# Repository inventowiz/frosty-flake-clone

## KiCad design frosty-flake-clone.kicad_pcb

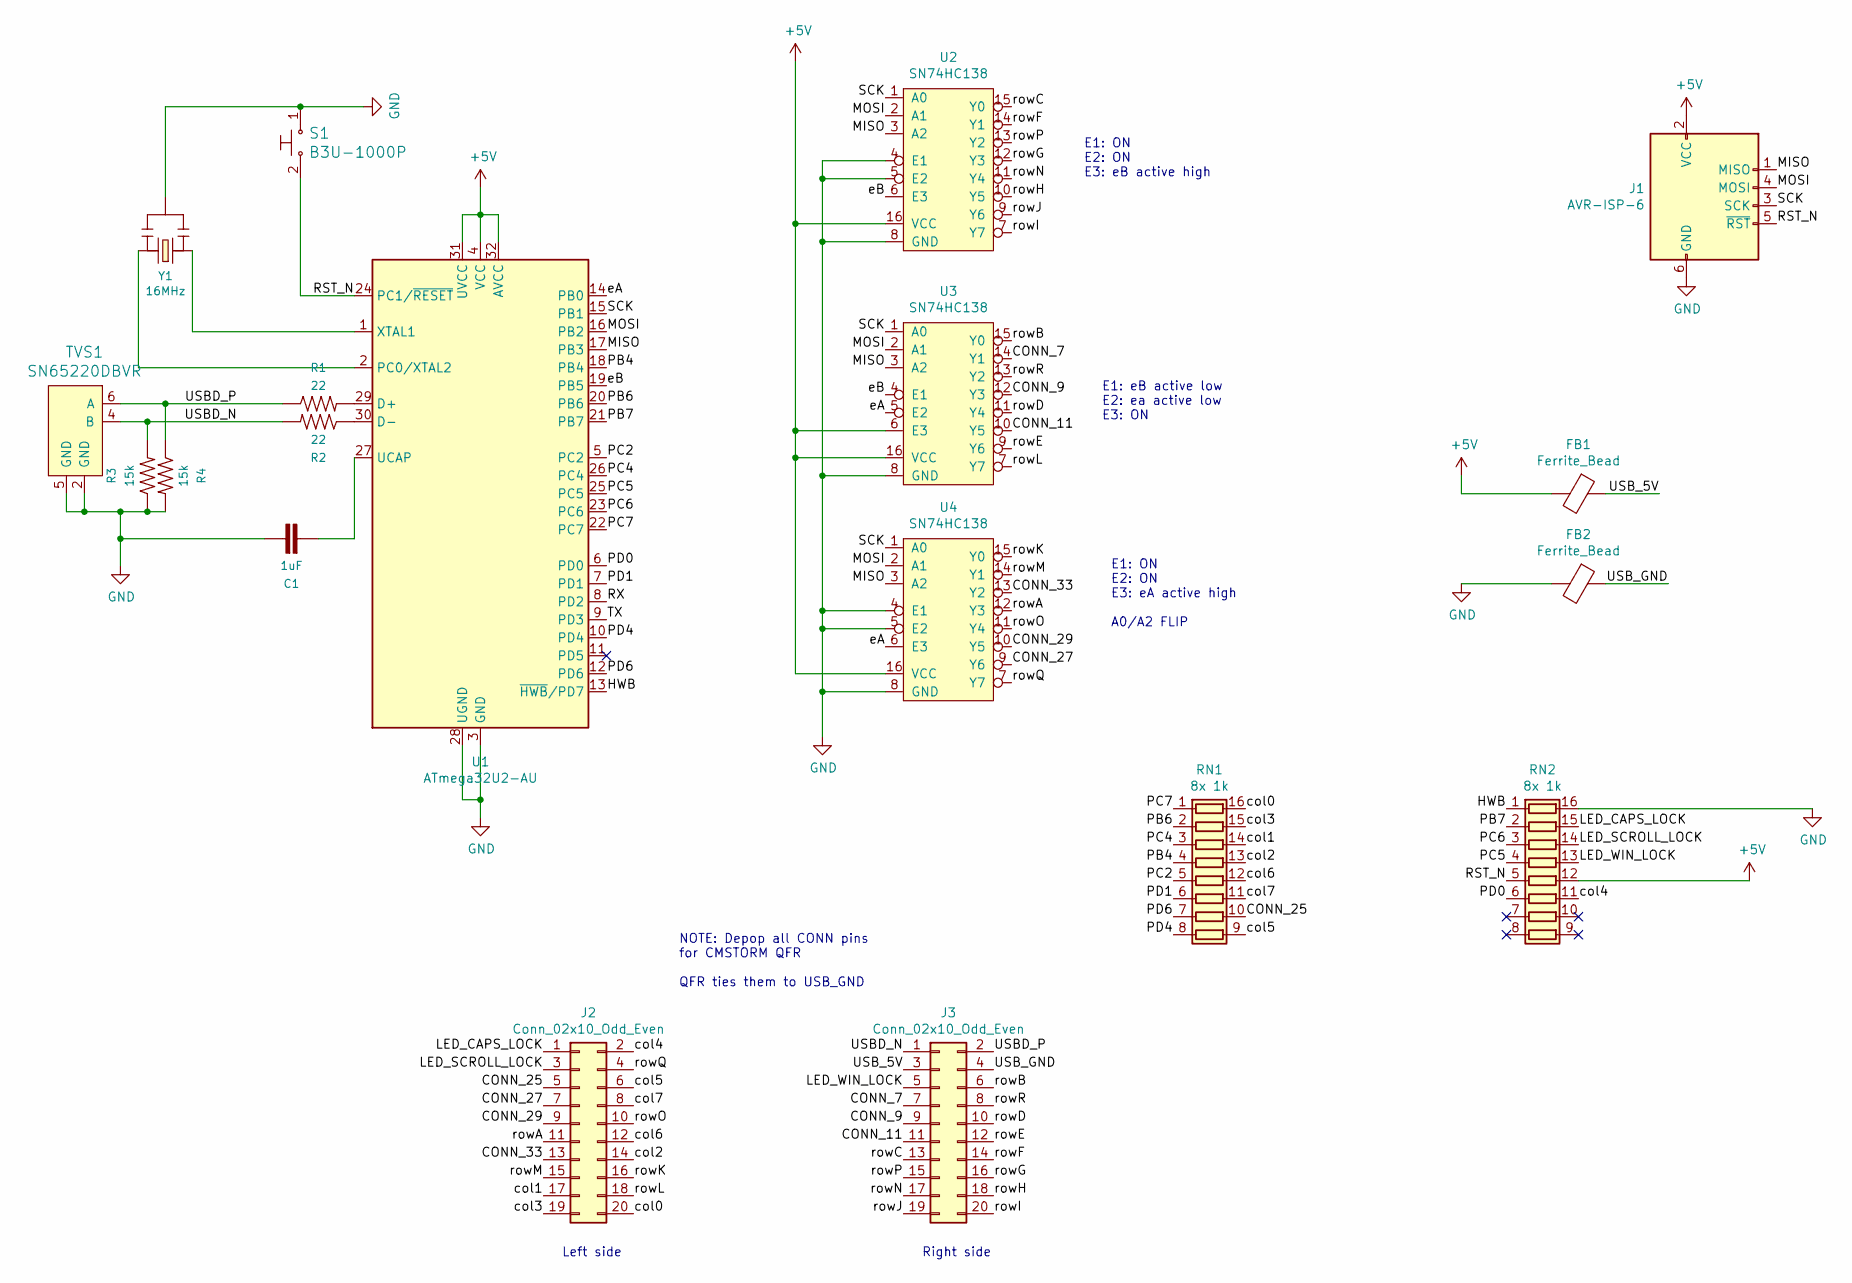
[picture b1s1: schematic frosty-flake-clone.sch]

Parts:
C1: 1uF; 0805
FB1, FB2: Ferrite_Bead; 0603
J1: AVR-ISP-6; 2X3
J2, J3: Conn_02x10_Odd_Even; PinHeader_2x10_P2.00mm_Vertical
R1, R2: 22; 0603
R3, R4: 15k; 0603
RN1, RN2: 8x 1k; R_Array_Convex_8x0602
S1: B3U-1000P; Switch_Tactile_SMD_B3U-1000P; MPN B3U-1000P; Digi-Key_PN SW1020CT-ND
TVS1: SN65220DBVR; SOT-23-6; MPN SN65220DBVR; Digi-Key_PN 296-9694-1-ND
U1: ATmega32U2-AU; TQFP-32_7x7mm_P0.8mm
U2, U3, U4: SN74HC138; TSSOP16
Y1: 16MHz; RESONATOR-SMD-3.2X1.3

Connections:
+5V: FB1.2, J1.2 (VCC), RN2.12 (R5.2), U1.4 (VCC), U1.31 (UVCC), U1.32 (AVCC), U2.16 (VCC), U3.6 (E3), U3.16 (VCC), U4.16 (VCC)
/CONN_7: J3.7, U3.14 (Y1)
/CONN_9: J3.9, U3.12 (Y3)
/CONN_11: J3.11, U3.10 (Y5)
/CONN_25: J2.5, RN1.10 (R7.2)
/CONN_27: J2.7, U4.9 (Y6)
/CONN_29: J2.9, U4.10 (Y5)
/CONN_33: J2.13, U4.13 (Y2)
/HWB: RN2.1 (R1.1), U1.13 (~HWB~/PD7)
/LED_CAPS_LOCK: J2.1, RN2.15 (R2.2)
/LED_SCROLL_LOCK: J2.3, RN2.14 (R3.2)
/LED_WIN_LOCK: J3.5, RN2.13 (R4.2)
/MISO: J1.1 (MISO), U1.17 (PB3), U2.3 (A2), U3.3 (A2), U4.3 (A2)
/MOSI: J1.4 (MOSI), U1.16 (PB2), U2.2 (A1), U3.2 (A1), U4.2 (A1)
/PB4: RN1.4 (R4.1), U1.18 (PB4)
/PB6: RN1.2 (R2.1), U1.20 (PB6)
/PB7: RN2.2 (R2.1), U1.21 (PB7)
/PC2: RN1.5 (R5.1), U1.5 (PC2)
/PC4: RN1.3 (R3.1), U1.26 (PC4)
/PC5: RN2.4 (R4.1), U1.25 (PC5)
/PC6: RN2.3 (R3.1), U1.23 (PC6)
/PC7: RN1.1 (R1.1), U1.22 (PC7)
/PD0: RN2.6 (R6.1), U1.6 (PD0)
/PD1: RN1.6 (R6.1), U1.7 (PD1)
/PD4: RN1.8 (R8.1), U1.10 (PD4)
/PD6: RN1.7 (R7.1), U1.12 (PD6)
/RST_N: J1.5 (~RST), RN2.5 (R5.1), S1.2, U1.24 (PC1/~RESET)
/RX: U1.8 (PD2)
/SCK: J1.3 (SCK), U1.15 (PB1), U2.1 (A0), U3.1 (A0), U4.1 (A0)
/TX: U1.9 (PD3)
/USBD_N: J3.1, R2.2, R3.2, TVS1.4 (B)
/USBD_P: J3.2, R1.1, R4.1, TVS1.6 (A)
/USB_5V: FB1.1, J3.3
/USB_GND: FB2.1, J3.4
/col0: J2.20, RN1.16 (R1.2)
/col1: J2.17, RN1.14 (R3.2)
/col2: J2.14, RN1.13 (R4.2)
/col3: J2.19, RN1.15 (R2.2)
/col4: J2.2, RN2.11 (R6.2)
/col5: J2.6, RN1.9 (R8.2)
/col6: J2.12, RN1.12 (R5.2)
/col7: J2.8, RN1.11 (R6.2)
/eA: U1.14 (PB0), U3.5 (E2), U4.6 (E3)
/eB: U1.19 (PB5), U2.6 (E3), U3.4 (E1)
/rowA: J2.11, U4.12 (Y3)
/rowB: J3.6, U3.15 (Y0)
/rowC: J3.13, U2.15 (Y0)
/rowD: J3.10, U3.11 (Y4)
/rowE: J3.12, U3.9 (Y6)
/rowF: J3.14, U2.14 (Y1)
/rowG: J3.16, U2.12 (Y3)
/rowH: J3.18, U2.10 (Y5)
/rowI: J3.20, U2.7 (Y7)
/rowJ: J3.19, U2.9 (Y6)
/rowK: J2.16, U4.15 (Y0)
/rowL: J2.18, U3.7 (Y7)
/rowM: J2.15, U4.14 (Y1)
/rowN: J3.17, U2.11 (Y4)
/rowO: J2.10, U4.11 (Y4)
/rowP: J3.15, U2.13 (Y2)
/rowQ: J2.4, U4.7 (Y7)
/rowR: J3.8, U3.13 (Y2)
GND: C1.1, FB2.2, J1.6 (GND), R3.1, R4.2, RN2.16 (R1.2), S1.1, TVS1.2 (GND), TVS1.5 (GND), U1.3 (GND), U1.28 (UGND), U2.4 (E1), U2.5 (E2), U2.8 (GND), U3.8 (GND), U4.4 (E1), U4.5 (E2), U4.8 (GND), Y1.2
unnamed: C1.2, U1.27 (UCAP)
unnamed: R1.2, U1.29 (D+)
unnamed: R2.1, U1.30 (D-)
unnamed: U1.1 (XTAL1), Y1.1
unnamed: U1.2 (PC0/XTAL2), Y1.3

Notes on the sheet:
Right side
Left side
E1: eB active low E2: ea active low E3: ON
E1: ON E2: ON E3: eB active high
E1: ON E2: ON E3: eA active high A0/A2 FLIP
NOTE: Depop all CONN pins for CMSTORM QFR QFR ties them to USB_GND

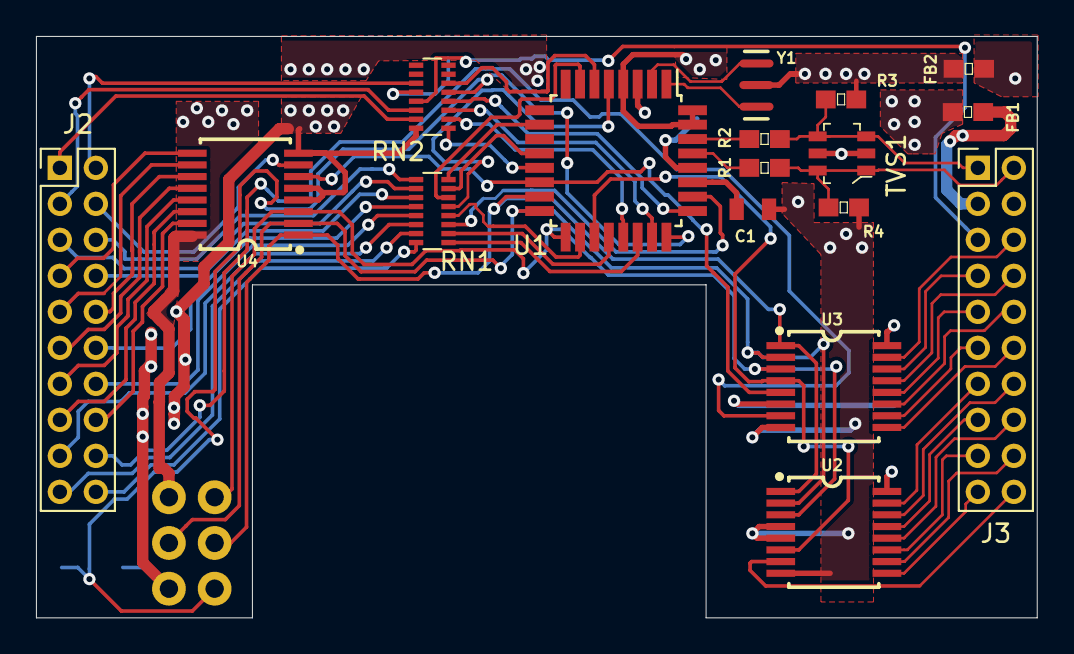
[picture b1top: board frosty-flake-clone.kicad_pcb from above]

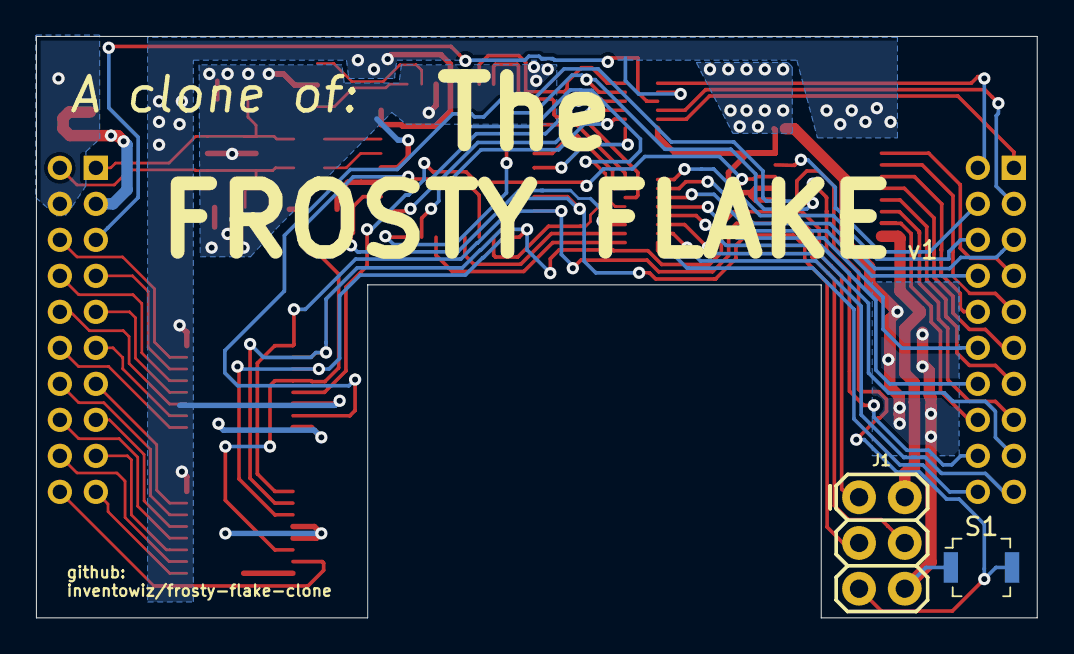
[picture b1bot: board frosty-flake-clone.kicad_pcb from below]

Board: 2 copper layers, 55.6 x 32.3 mm, 19 parts (2 on the bottom side), 66 nets.

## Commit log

2020-03-29 add base project
